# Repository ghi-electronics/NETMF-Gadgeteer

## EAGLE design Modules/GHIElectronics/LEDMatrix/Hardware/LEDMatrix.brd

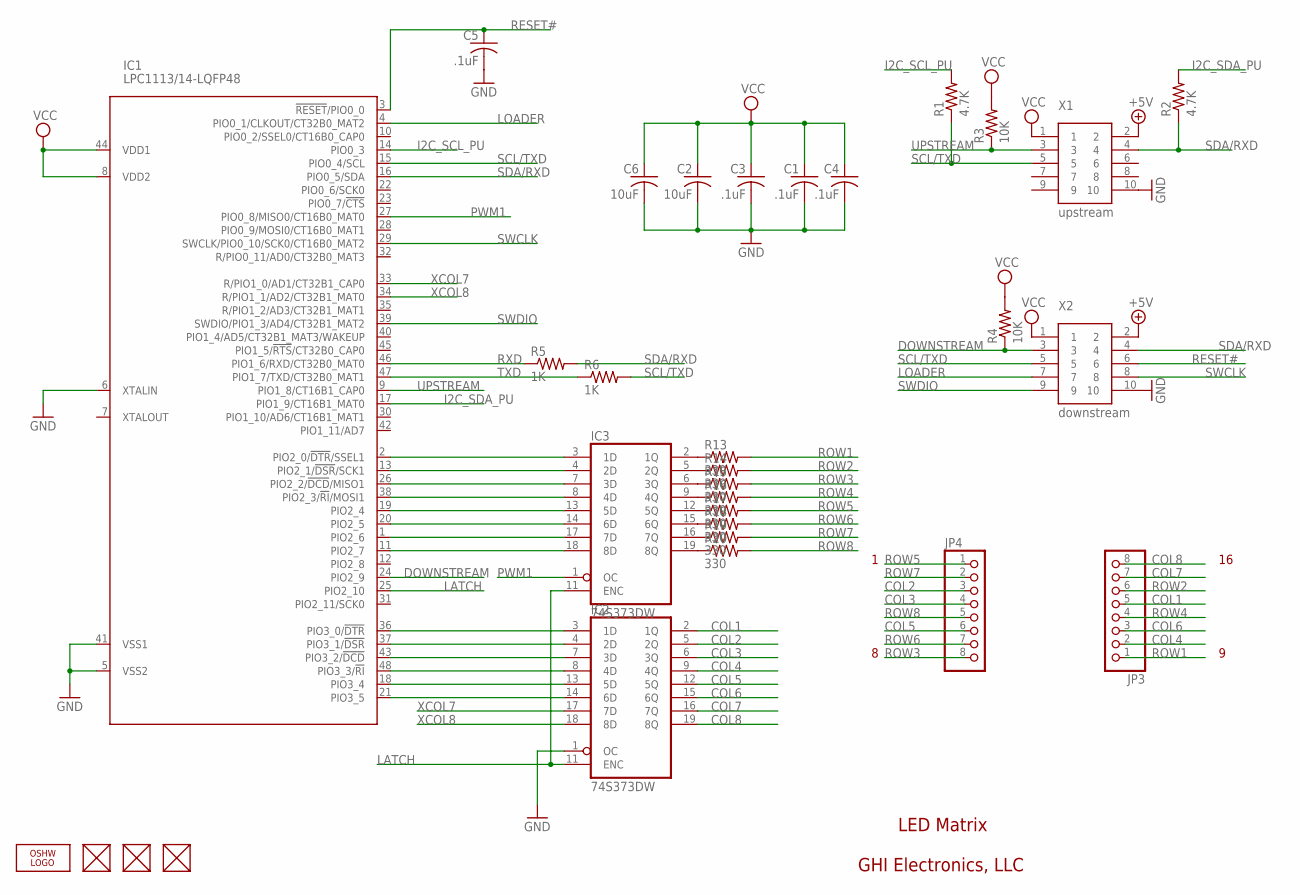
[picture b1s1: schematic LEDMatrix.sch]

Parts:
C1, C3, C4, C5: .1uF; C0603K
C2, C6: 10uF; C0805K
FUD1, FUD2, FUD3: FIDUCIAL; FIDUCIAL_40MIL
IC1: LPC1113/14-LQFP48; LQFP48
IC2, IC3: 74S373DW; SO20W
JP3, JP4: PINHD-1X8; 1X08
LOGO: LOGO-OSHW-FILLX0200-NT; OSHW_FILLX200_NOTEXT
R1, R2: 4.7K; R0603
R3, R4: 10K; R0603
R5, R6: 1K; R0603
R13, R14, R15, R16, R17, R18, R19, R20: 330; R0603
X1: upstream; 2X5_1.27MM
X2: downstream; 2X5_1.27MM

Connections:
+5V: X1.2, X2.2
COL1: IC2.2 (1Q), JP3.5
COL2: IC2.5 (2Q), JP4.3
COL3: IC2.6 (3Q), JP4.4
COL4: IC2.9 (4Q), JP3.2
COL5: IC2.12 (5Q), JP4.6
COL6: IC2.15 (6Q), JP3.3
COL7: IC2.16 (7Q), JP3.7
COL8: IC2.19 (8Q), JP3.8
DOWNSTREAM: IC1.24 (PIO2_9), R4.1, X2.3
GND: C1.2, C2.2, C3.2, C4.2, C5.2, C6.2, IC1.5 (VSS2), IC1.6 (XTALIN), IC1.41 (VSS1), IC2.1 (OC), IC2.10 (GND), IC3.10 (GND), X1.10, X2.10
I2C_SCL_PU: IC1.14 (PIO0_3), R1.2
I2C_SDA_PU: IC1.17 (PIO1_9/CT16B1_MAT0), R2.2
LATCH: IC1.25 (PIO2_10), IC2.11 (ENC), IC3.11 (ENC)
LOADER: IC1.4 (PIO0_1/CLKOUT/CT32B0_MAT2), X2.7
unnamed: IC1.36 (PIO3_0/!DTR!), IC2.3 (1D)
unnamed: IC1.37 (PIO3_1/!DSR!), IC2.4 (2D)
unnamed: IC1.43 (PIO3_2/!DCD!), IC2.7 (3D)
unnamed: IC1.48 (PIO3_3/!RI!), IC2.8 (4D)
unnamed: IC1.18 (PIO3_4), IC2.13 (5D)
unnamed: IC1.21 (PIO3_5), IC2.14 (6D)
unnamed: IC3.2 (1Q), R13.1
unnamed: IC1.2 (PIO2_0/!DTR!/SSEL1), IC3.3 (1D)
unnamed: IC1.13 (PIO2_1/!DSR!/SCK1), IC3.4 (2D)
unnamed: IC1.26 (PIO2_2/!DCD!/MISO1), IC3.7 (3D)
unnamed: IC1.38 (PIO2_3/!RI!/MOSI1), IC3.8 (4D)
unnamed: IC3.5 (2Q), R14.1
unnamed: IC1.19 (PIO2_4), IC3.13 (5D)
unnamed: IC1.20 (PIO2_5), IC3.14 (6D)
unnamed: IC1.1 (PIO2_6), IC3.17 (7D)
unnamed: IC1.11 (PIO2_7), IC3.18 (8D)
unnamed: IC3.6 (3Q), R15.1
unnamed: IC3.9 (4Q), R16.1
unnamed: IC3.12 (5Q), R17.1
unnamed: IC3.15 (6Q), R18.1
unnamed: IC3.16 (7Q), R19.1
unnamed: IC3.19 (8Q), R20.1
PWM1: IC1.27 (PIO0_8/MISO0/CT16B0_MAT0), IC3.1 (OC)
RESET#: C5.1, IC1.3 (!RESET!/PIO0_0), X2.6
ROW1: JP3.1, R13.2
ROW2: JP3.6, R14.2
ROW3: JP4.8, R15.2
ROW4: JP3.4, R16.2
ROW5: JP4.1, R17.2
ROW6: JP4.7, R18.2
ROW7: JP4.2, R19.2
ROW8: JP4.5, R20.2
RXD: IC1.46 (PIO1_6/RXD/CT32B0_MAT0), R5.1
SCL/TXD: IC1.15 (PIO0_4/SCL), R1.1, R6.2, X1.5, X2.5
SDA/RXD: IC1.16 (PIO0_5/SDA), R2.1, R5.2, X1.4, X2.4
SWCLK: IC1.29 (SWCLK/PIO0_10/SCK0/CT16B0_MAT2), X2.8
SWDIO: IC1.39 (SWDIO/PIO1_3/AD4/CT32B1_MAT2), X2.9
TXD: IC1.47 (PIO1_7/TXD/CT32B0_MAT1), R6.1
UPSTREAM: IC1.9 (PIO1_8/CT16B1_CAP0), R3.1, X1.3
VCC: C1.1, C2.1, C3.1, C4.1, C6.1, IC1.8 (VDD2), IC1.44 (VDD1), IC2.20 (VCC), IC3.20 (VCC), R3.2, R4.2, X1.1, X2.1
XCOL7: IC1.33 (R/PIO1_0/AD1/CT32B1_CAP0), IC2.17 (7D)
XCOL8: IC1.34 (R/PIO1_1/AD2/CT32B1_MAT0), IC2.18 (8D)

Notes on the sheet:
LED Matrix
GHI Electronics, LLC

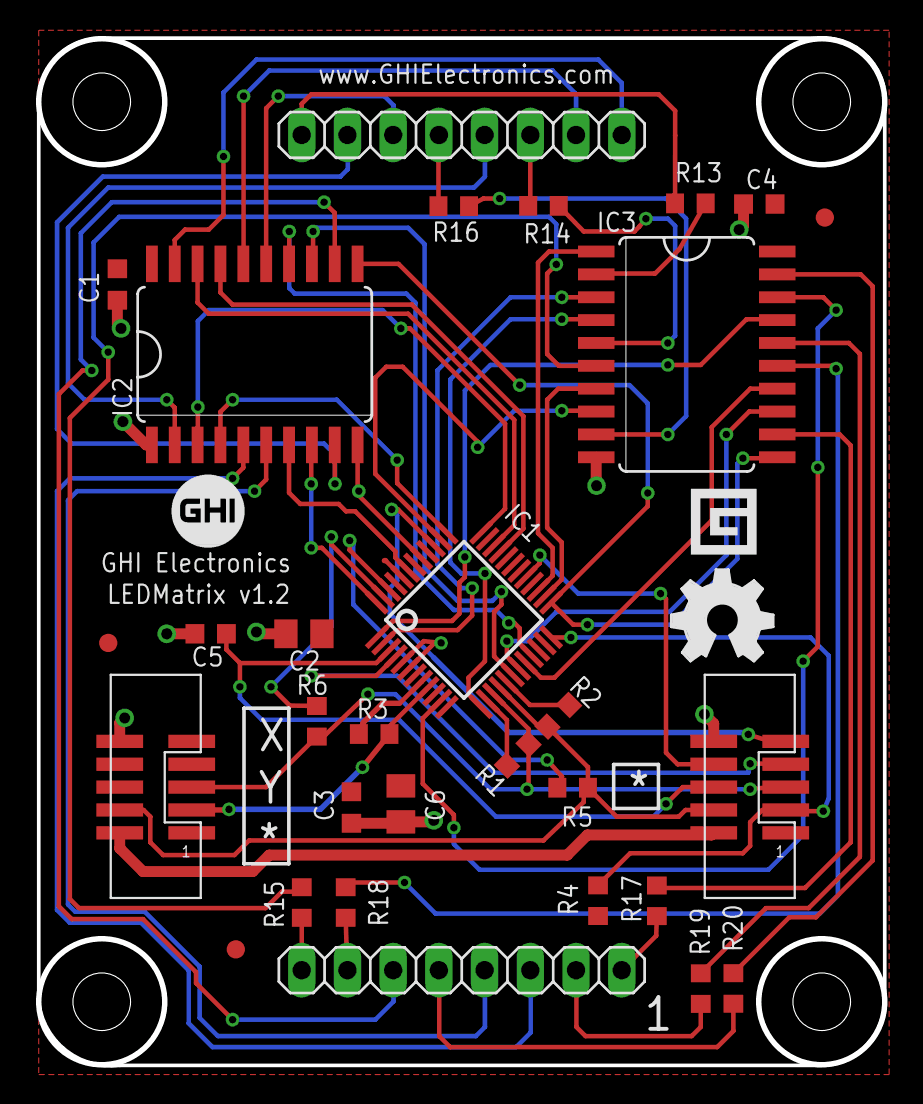
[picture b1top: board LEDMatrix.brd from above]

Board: 2 copper layers, 47.0 x 57.1 mm, 31 parts (0 on the bottom side), 57 nets.

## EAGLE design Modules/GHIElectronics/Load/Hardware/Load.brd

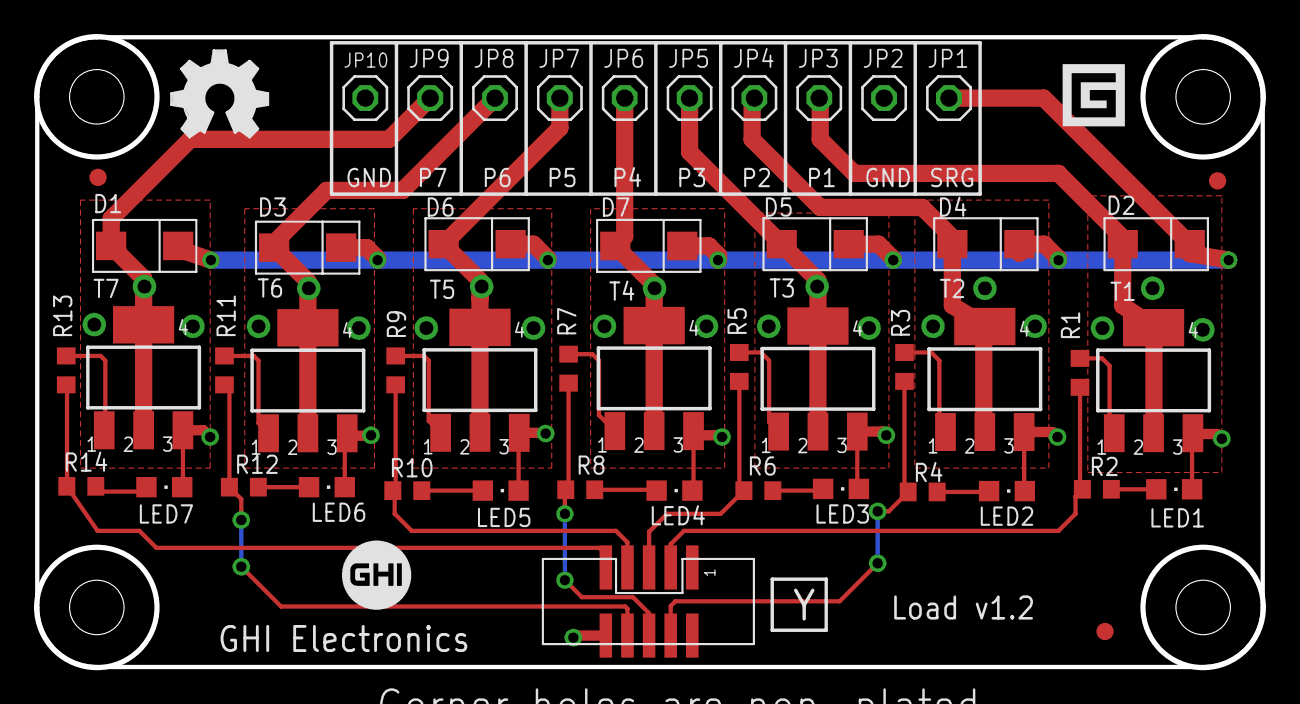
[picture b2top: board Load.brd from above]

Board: 2 copper layers, 72.0 x 37.0 mm, 50 parts (0 on the bottom side), 30 nets.

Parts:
D1, D2, D3, D4, D5, D6, D7: STPS140A; DIODE_SMA
FUD1, FUD2, FUD3: FIDUCIAL; FIDUCIAL_40MIL
JP1, JP2, JP3, JP4, JP5, JP6, JP7, JP8, JP9, JP10: 1X01
LED1, LED2, LED3, LED4, LED5, LED6, LED7: Red; CHIPLED_0805
LOGO1: LOGO-OSHW-FILLX0200-NT; OSHW_FILLX200_NOTEXT
R1, R3, R5, R7, R9, R11, R13: 330; R0603
R2, R4, R6, R8, R10, R12, R14: 1K; R0603
T1: BCP55FSTR-ND; SOT223
T2, T3, T4, T5, T6, T7: SOT223
X1: 2X5_1.27MM

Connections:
GND: JP2.1, JP10.1, LED1.C, LED2.C, LED3.C, LED4.C, LED5.C, LED6.C, LED7.C, T1.3, T2.3, T3.3, T4.3, T5.3, T6.3, T7.3, X1.10
unnamed: R1.2, T1.1
unnamed: R5.2, T3.1
unnamed: R7.2, T4.1
unnamed: D2.A, JP3.1, T1.2, T1.4
unnamed: D4.A, JP4.1, T2.2, T2.4
unnamed: D5.A, JP5.1, T3.2, T3.4
unnamed: D7.A, JP6.1, T4.2, T4.4
unnamed: D6.A, JP7.1, T5.2, T5.4
unnamed: D3.A, JP8.1, T6.2, T6.4
unnamed: D1.A, JP9.1, T7.2, T7.4
unnamed: R9.2, T5.1
unnamed: R3.2, T2.1
unnamed: R11.2, T6.1
unnamed: R13.2, T7.1
unnamed: D1.K, D2.K, D3.K, D4.K, D5.K, D6.K, D7.K, JP1.1
unnamed: LED1.A, R2.2
unnamed: LED2.A, R4.2
unnamed: LED3.A, R6.2
unnamed: LED4.A, R8.2
unnamed: LED5.A, R10.2
unnamed: LED6.A, R12.2
unnamed: LED7.A, R14.2
PIN3: R1.1, R2.1, X1.3
PIN4: R3.1, R4.1, X1.4
PIN5: R5.1, R6.1, X1.5
PIN6: R7.1, R8.1, X1.6
PIN7: R9.1, R10.1, X1.7
PIN8: R11.1, R12.1, X1.8
PIN9: R13.1, R14.1, X1.9
